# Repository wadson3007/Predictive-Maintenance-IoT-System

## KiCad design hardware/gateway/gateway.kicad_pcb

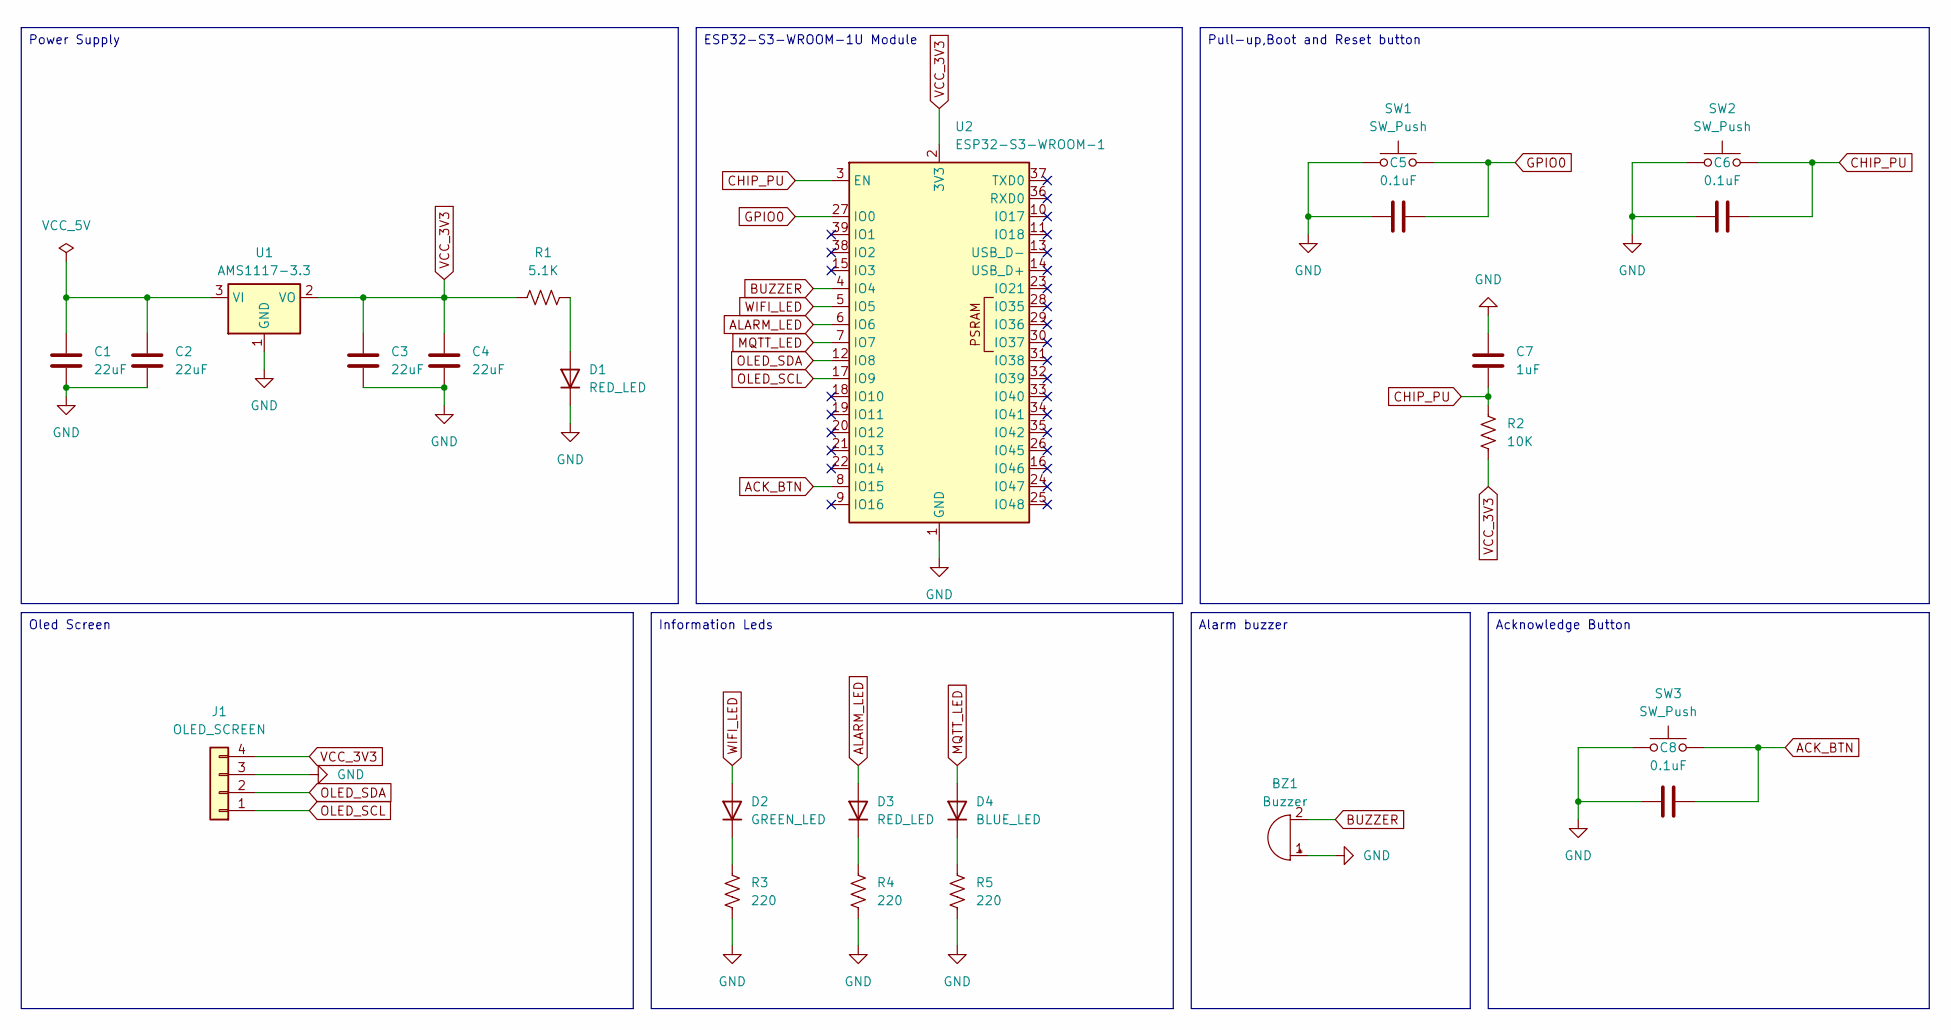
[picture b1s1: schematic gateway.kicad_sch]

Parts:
BZ1: Buzzer; Buzzer_12x9.5RM7.6
C1, C2, C3, C4: 22uF; CP_Radial_D5.0mm_P2.00mm
C5, C6, C8: 0.1uF; C_Disc_D5.0mm_W2.5mm_P5.00mm
C7: 1uF; C_Disc_D5.0mm_W2.5mm_P5.00mm
D1, D3: RED_LED; LED_D5.0mm
D2: GREEN_LED; LED_D5.0mm
D4: BLUE_LED; LED_D5.0mm
J1: OLED_SCREEN; PinHeader_1x04_P2.54mm_Vertical
R1: 5.1K; R_Axial_DIN0207_L6.3mm_D2.5mm_P7.62mm_Horizontal
R2: 10K; R_Axial_DIN0207_L6.3mm_D2.5mm_P7.62mm_Horizontal
R3, R4, R5: 220; R_Axial_DIN0207_L6.3mm_D2.5mm_P7.62mm_Horizontal
SW1, SW2, SW3: SW_Push; SW_PUSH_6mm
U1: AMS1117-3.3; SOT-223-3_TabPin2
U2: ESP32-S3-WROOM-1

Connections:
ACK_BTN: C8.1, SW3.2, U2.8 (IO15)
ALARM_LED: D3.2 (A), U2.6 (IO6)
BUZZER: BZ1.2 (-), U2.4 (IO4)
CHIP_PU: C6.1, C7.2, R2.1, SW2.2, U2.3 (EN)
GND: BZ1.1 (+), C1.2, C2.2, C3.2, C4.2, C5.2, C6.2, C7.1, C8.2, D1.1 (K), J1.3, R3.2, R4.2, R5.2, SW1.1, SW2.1, SW3.1, U1.1 (GND), U2.1 (GND), U2.40 (GND), U2.41 (GND)
GPIO0: C5.1, SW1.2, U2.27 (IO0)
MQTT_LED: D4.2 (A), U2.7 (IO7)
unnamed: D1.2 (A), R1.2
unnamed: D2.1 (K), R3.1
unnamed: D3.1 (K), R4.1
unnamed: D4.1 (K), R5.1
unnamed: C1.1, C2.1, U1.3 (VI)
OLED_SCL: J1.1, U2.17 (IO9)
OLED_SDA: J1.2, U2.12 (IO8)
VCC_3V3: C3.1, C4.1, J1.4, R1.1, R2.2, U1.2 (VO), U2.2 (3V3)
WIFI_LED: D2.2 (A), U2.5 (IO5)

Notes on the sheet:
Alarm buzzer
Acknowledge Button
Pull-up,Boot and Reset button
ESP32-S3-WROOM-1U Module
Information Leds
Oled Screen
Power Supply

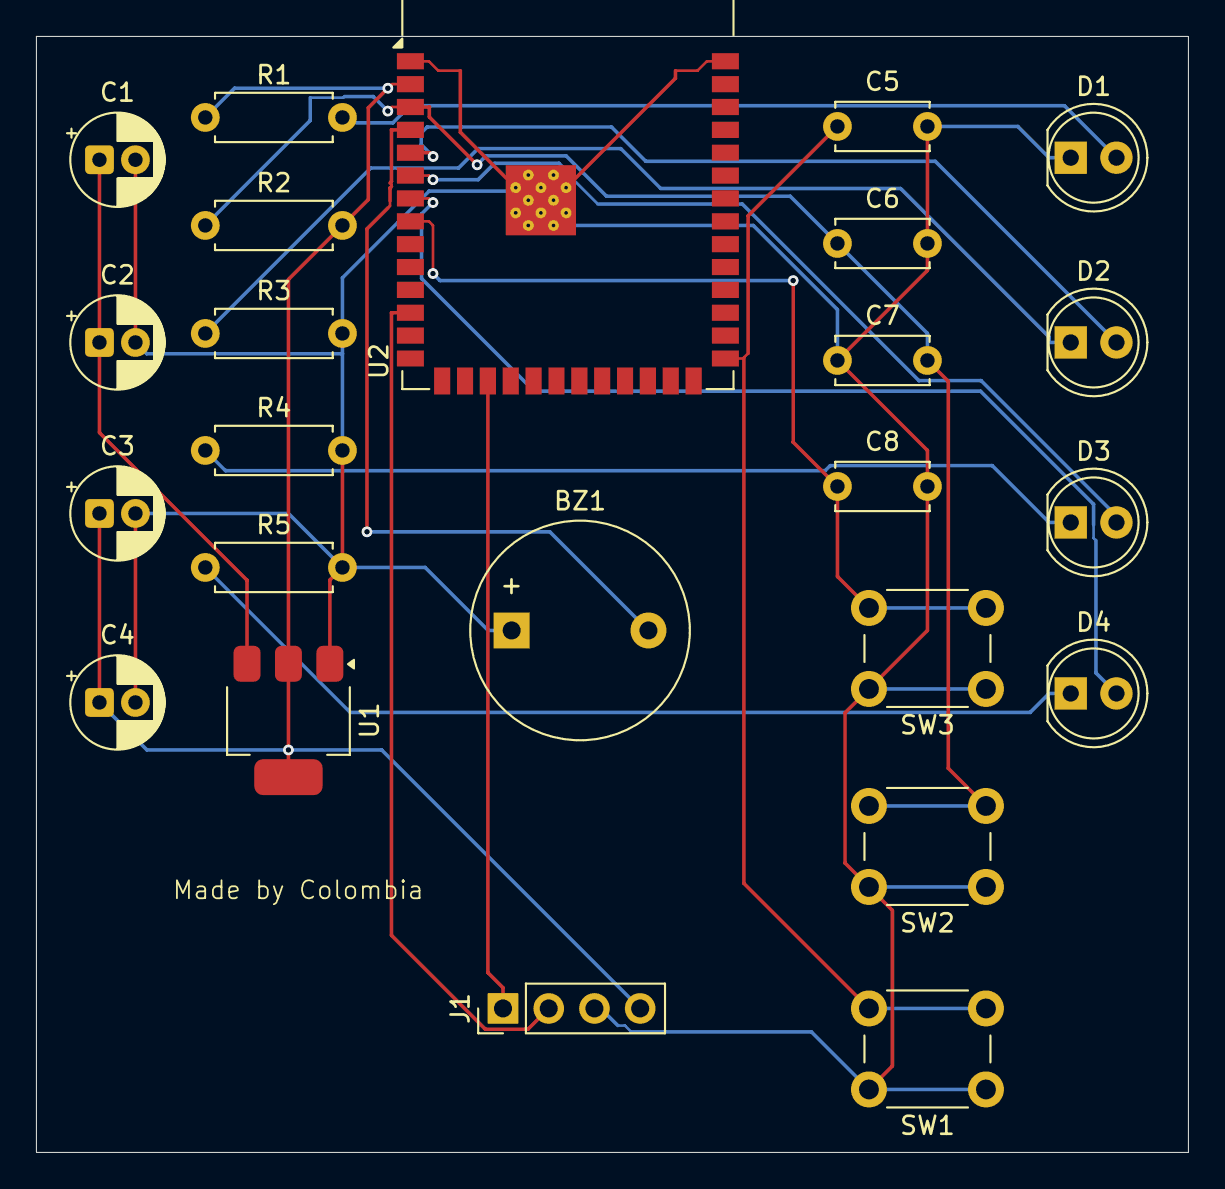
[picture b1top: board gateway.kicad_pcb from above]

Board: 2 copper layers, 64.0 x 62.0 mm, 24 parts (0 on the bottom side), 16 nets.

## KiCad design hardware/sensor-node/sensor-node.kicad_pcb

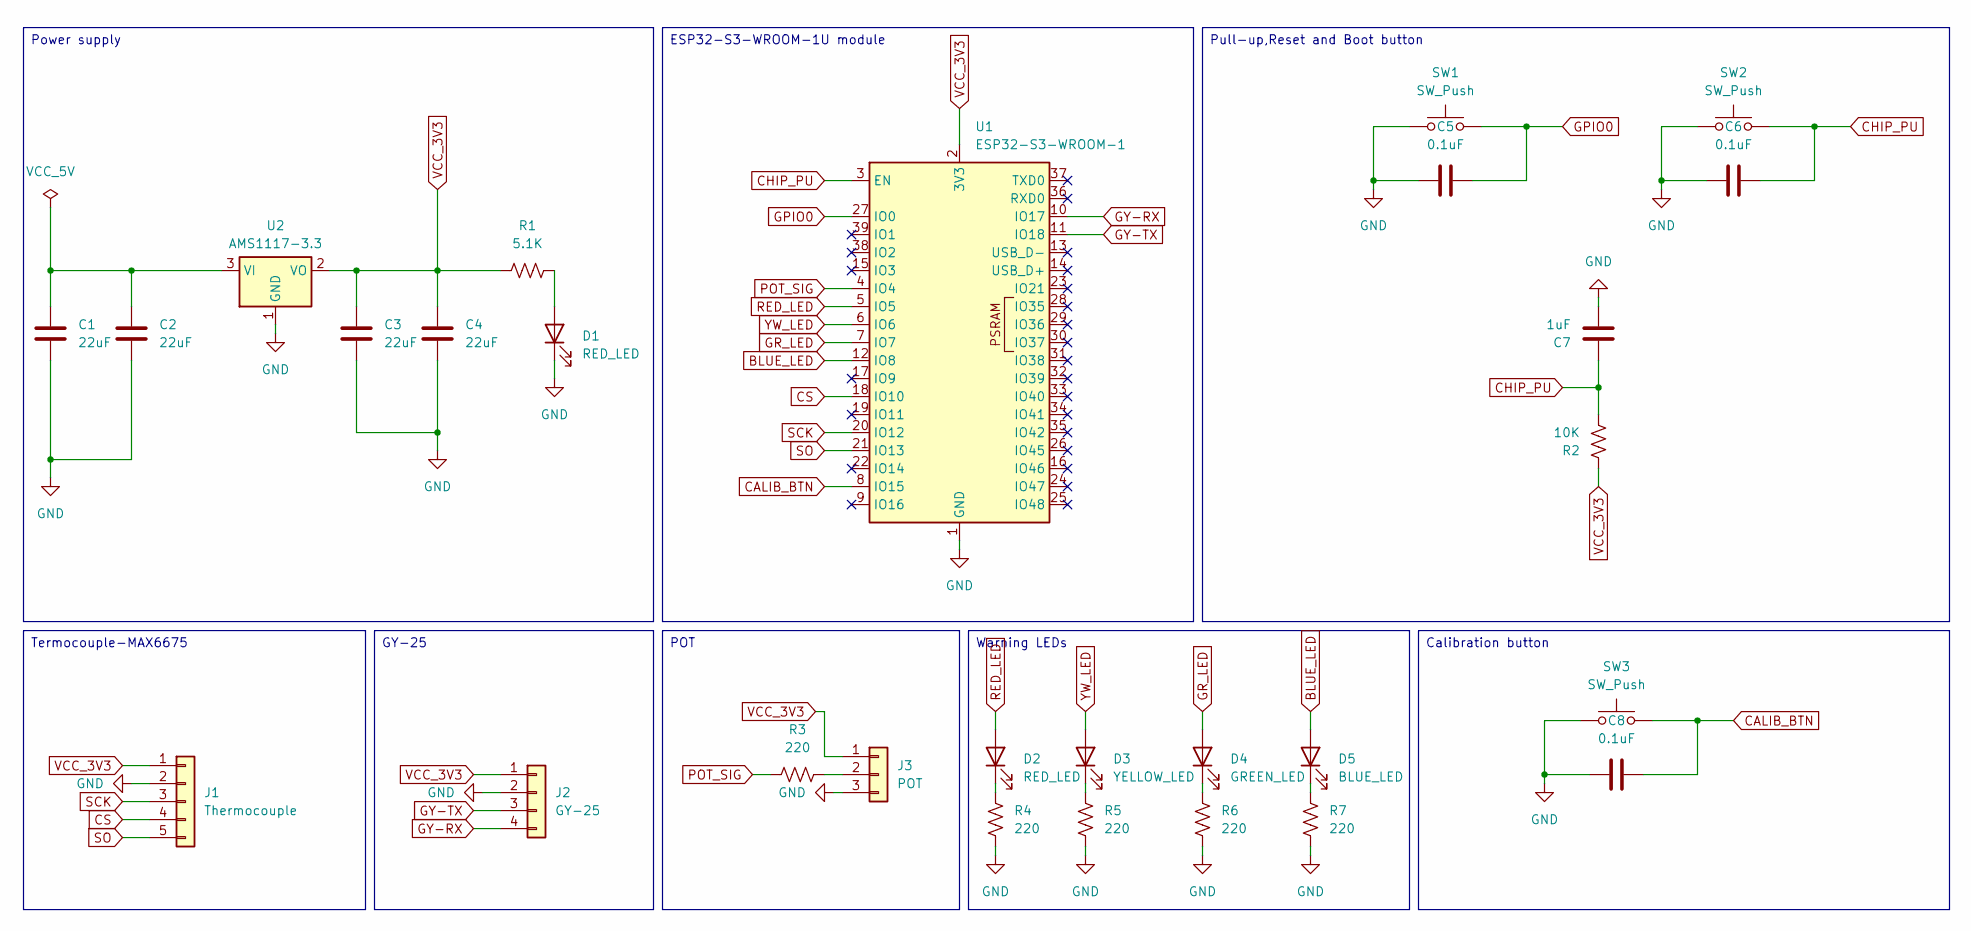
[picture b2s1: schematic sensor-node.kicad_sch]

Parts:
C1, C2, C3, C4: 22uF; CP_Radial_D5.0mm_P2.00mm
C5, C6, C8: 0.1uF; C_Disc_D5.0mm_W2.5mm_P5.00mm
C7: 1uF; CP_Radial_D5.0mm_P2.00mm
D1, D2: RED_LED; LED_D5.0mm
D3: YELLOW_LED; LED_D5.0mm
D4: GREEN_LED; LED_D5.0mm
D5: BLUE_LED; LED_D5.0mm
J1: Thermocouple; PinHeader_1x05_P2.54mm_Vertical
J2: GY-25; PinHeader_1x04_P2.54mm_Vertical
J3: POT; PinHeader_1x03_P2.54mm_Vertical
R1: 5.1K; R_Axial_DIN0207_L6.3mm_D2.5mm_P7.62mm_Horizontal
R2: 10K; R_Axial_DIN0207_L6.3mm_D2.5mm_P7.62mm_Horizontal
R3, R4, R5, R6, R7: 220; R_Axial_DIN0207_L6.3mm_D2.5mm_P7.62mm_Horizontal
SW1, SW2, SW3: SW_Push; SW_PUSH_6mm
U1: ESP32-S3-WROOM-1
U2: AMS1117-3.3; SOT-223-3_TabPin2

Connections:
BLUE_LED: D5.2 (A), U1.12 (IO8)
CALIB_BTN: C8.2, SW3.2, U1.8 (IO15)
CHIP_PU: C6.2, C7.1, R2.1, SW2.2, U1.3 (EN)
CS: J1.4, U1.18 (IO10)
GND: C1.2, C2.2, C3.2, C4.2, C5.1, C6.1, C7.2, C8.1, D1.1 (K), J1.2, J2.2, J3.3, R4.1, R5.1, R6.1, R7.1, SW1.1, SW2.1, SW3.1, U1.1 (GND), U1.40 (GND), U1.41 (GND), U2.1 (GND)
GPIO0: C5.2, SW1.2, U1.27 (IO0)
GR_LED: D4.2 (A), U1.7 (IO7)
GY-RX: J2.4, U1.10 (IO17)
GY-TX: J2.3, U1.11 (IO18)
unnamed: D1.2 (A), R1.1
unnamed: D2.1 (K), R4.2
unnamed: D3.1 (K), R5.2
unnamed: D4.1 (K), R6.2
unnamed: D5.1 (K), R7.2
unnamed: J3.2, R3.1
unnamed: C1.1, C2.1, U2.3 (VI)
POT_SIG: R3.2, U1.4 (IO4)
RED_LED: D2.2 (A), U1.5 (IO5)
SCK: J1.3, U1.20 (IO12)
SO: J1.5, U1.21 (IO13)
VCC_3V3: C3.1, C4.1, J1.1, J2.1, J3.1, R1.2, R2.2, U1.2 (3V3), U2.2 (VO)
YW_LED: D3.2 (A), U1.6 (IO6)

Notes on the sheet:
POT
Warning LEDs
Termocouple-MAX6675
Pull-up,Reset and Boot button
Power supply
Calibration button
ESP32-S3-WROOM-1U module
GY-25

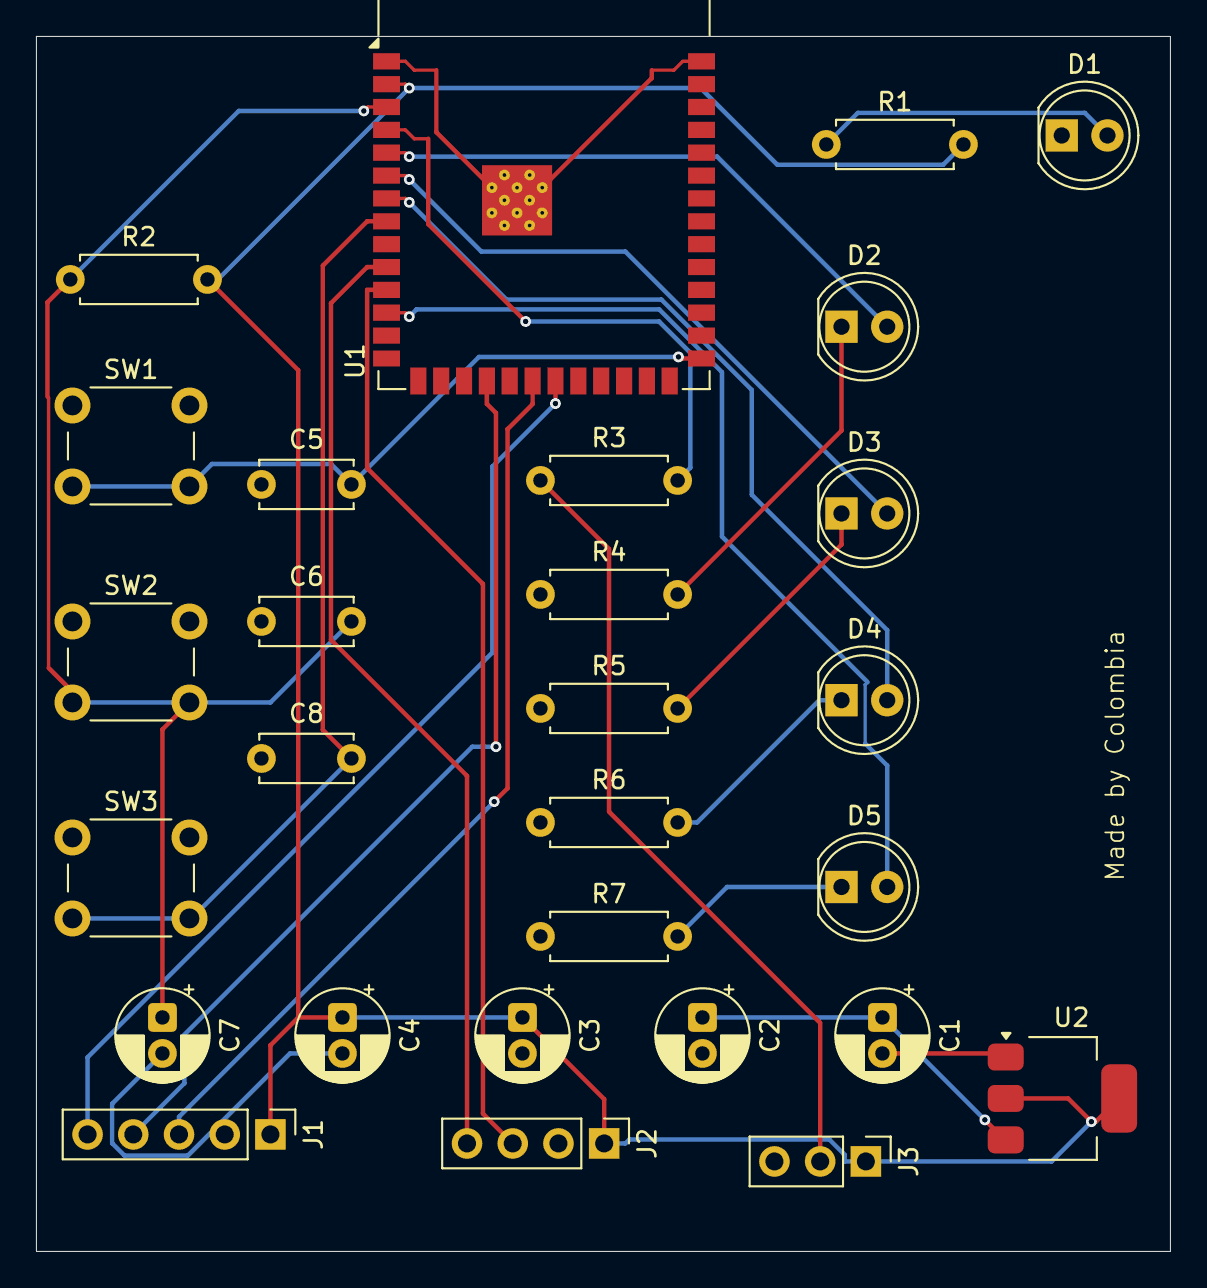
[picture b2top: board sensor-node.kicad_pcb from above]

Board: 2 copper layers, 63.0 x 67.5 mm, 28 parts (0 on the bottom side), 22 nets.
